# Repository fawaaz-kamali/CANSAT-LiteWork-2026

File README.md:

# CANSAT-LiteWork-2026
Repository containing major program files and schematics for Team 'Lite Work for the TMU CANSAT STEC Initiative 

Team Members: Fawaaz Kamali Siddiqui, Ben Reboks, Basim Allawala, Hamid Karimi, Mohammad Alwattar

## ESP32 Flight Computer

### Overview

The flight computer designed in the PDR phase of the competition is simply named the ESP32 Flight Computer. The circuit was designed 
entirely in KiCad and the microcontroller for the circuit is the ESP32-S3-WROOM-1. 

The parts list for this circuit is as follows:

| Model | Description |
|---|---|
| ESP32-S3-WROOM-1 | Microcontroller Unit |
| ICM-42670-L | Inertial Measurement Unit |
| ICP-20100 | Barometric Pressure Sensor |
| NEO-6M Breakout Board | GPS Module |
| 2 x SG90 | Servo Motors |
| 1S 18605 LiFePO4 | Battery |

#### KiCad Files
<div align="center">
  <div>

    <p><em>3D Render</em></p>
  </div>
  <br>

  <div>
    <br>
    <p><em>Schematic</em></p>
  </div>
  <br>
  
  <div>
    
    <br>
    <em>Footprint</em>
  </div>
</div>

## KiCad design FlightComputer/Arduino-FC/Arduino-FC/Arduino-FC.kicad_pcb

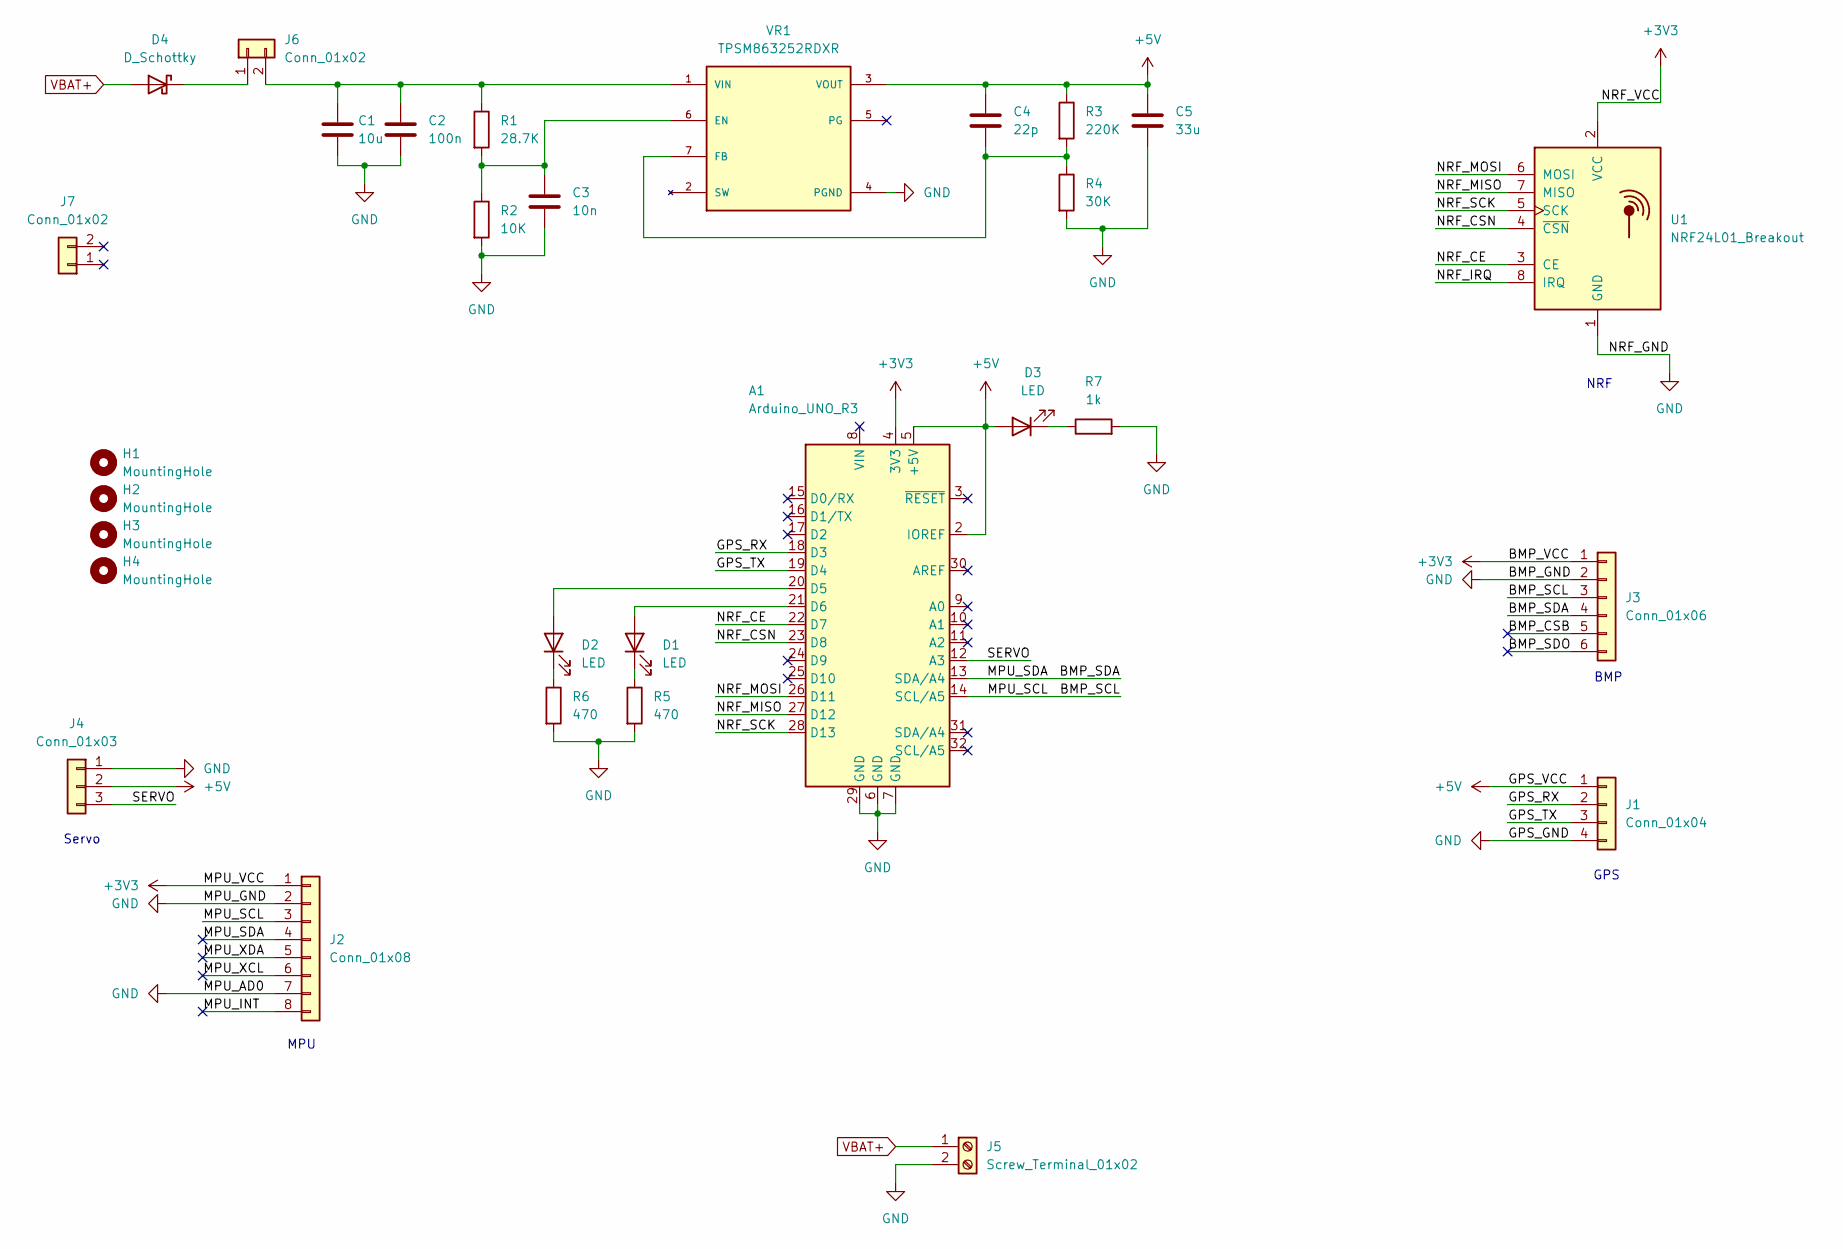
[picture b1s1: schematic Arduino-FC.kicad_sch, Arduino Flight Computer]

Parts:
A1: Arduino_UNO_R3
C1: 10u; C_0805_2012Metric_Pad1.18x1.45mm_HandSolder
C2: 100n; C_0805_2012Metric_Pad1.18x1.45mm_HandSolder
C3: 10n; C_0402_1005Metric_Pad0.74x0.62mm_HandSolder
C4: 22p; C_0402_1005Metric_Pad0.74x0.62mm_HandSolder
C5: 33u; C_1812_4532Metric_Pad1.57x3.40mm_HandSolder
D1, D2, D3: LED; LED_D5.0mm_Clear
D4: D_Schottky; DO-214AC
H1, H2, H3, H4: MountingHole; MountingHole_2.2mm_M2
J1: Conn_01x04; PinHeader_1x04_P2.54mm_Vertical
J2: Conn_01x08; PinHeader_1x08_P2.54mm_Vertical
J3: Conn_01x06; PinHeader_1x06_P2.54mm_Vertical
J4: Conn_01x03; PinHeader_1x03_P2.54mm_Vertical
J5: Screw_Terminal_01x02; TerminalBlock_MaiXu_MX126-5.0-02P_1x02_P5.00mm; LCSC C8465
J6, J7: Conn_01x02; PinHeader_1x02_P2.54mm_Vertical
R1: 28.7K; R_0402_1005Metric_Pad0.72x0.64mm_HandSolder
R2: 10K; R_0402_1005Metric_Pad0.72x0.64mm_HandSolder
R3: 220K; R_0603_1608Metric_Pad0.98x0.95mm_HandSolder
R4: 30K; R_0603_1608Metric_Pad0.98x0.95mm_HandSolder
R5, R6: 470; R_Axial_DIN0414_L11.9mm_D4.5mm_P15.24mm_Horizontal
R7: 1k; R_Axial_DIN0414_L11.9mm_D4.5mm_P15.24mm_Horizontal
U1: NRF24L01_Breakout; nRF24L01-Adapter
VR1: TPSM863252RDXR; VREG_TPSM863252RDXR; PARTREV B

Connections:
+3V3: A1.4 (3V3), J2.1, J3.1, U1.2 (VCC)
+5V: A1.2 (IOREF), A1.5 (+5V), C4.1, C5.1, D3.2 (A), J1.1, J4.2, R3.1, VR1.3 (VOUT)
/BMP_CSB: J3.5
/BMP_SCL: A1.14 (SCL/A5), J2.3, J3.3
/BMP_SDA: A1.13 (SDA/A4), J2.4, J3.4
/BMP_SDO: J3.6
/GPS_RX: A1.18 (D3), J1.2
/GPS_TX: A1.19 (D4), J1.3
/MPU_INT: J2.8
/MPU_XCL: J2.6
/MPU_XDA: J2.5
/NRF_CE: A1.22 (D7), U1.3 (CE)
/NRF_CSN: A1.23 (D8), U1.4 (~CSN)
/NRF_IRQ: U1.8 (IRQ)
/NRF_MISO: A1.27 (D12), U1.7 (MISO)
/NRF_MOSI: A1.26 (D11), U1.6 (MOSI)
/NRF_SCK: A1.28 (D13), U1.5 (SCK)
/SERVO: A1.12 (A3), J4.3
GND: A1.6 (GND), A1.7 (GND), A1.29 (GND), C1.2, C2.2, C3.2, C5.2, J1.4, J2.2, J2.7, J3.2, J4.1, J5.2, R2.2, R4.2, R5.2, R6.2, R7.2, U1.1 (GND), VR1.4 (PGND)
unnamed: A1.20 (D5), D2.2 (A)
unnamed: A1.21 (D6), D1.2 (A)
unnamed: D1.1 (K), R5.1
unnamed: D2.1 (K), R6.1
unnamed: D3.1 (K), R7.1
unnamed: D4.1 (K), J6.1
unnamed: C1.1, C2.1, J6.2, R1.1, VR1.1 (VIN)
unnamed: C3.1, R1.2, R2.1, VR1.6 (EN)
unnamed: C4.2, R3.2, R4.1, VR1.7 (FB)
VBAT+: D4.2 (A), J5.1

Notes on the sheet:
GPS
NRF
Servo
BMP
MPU

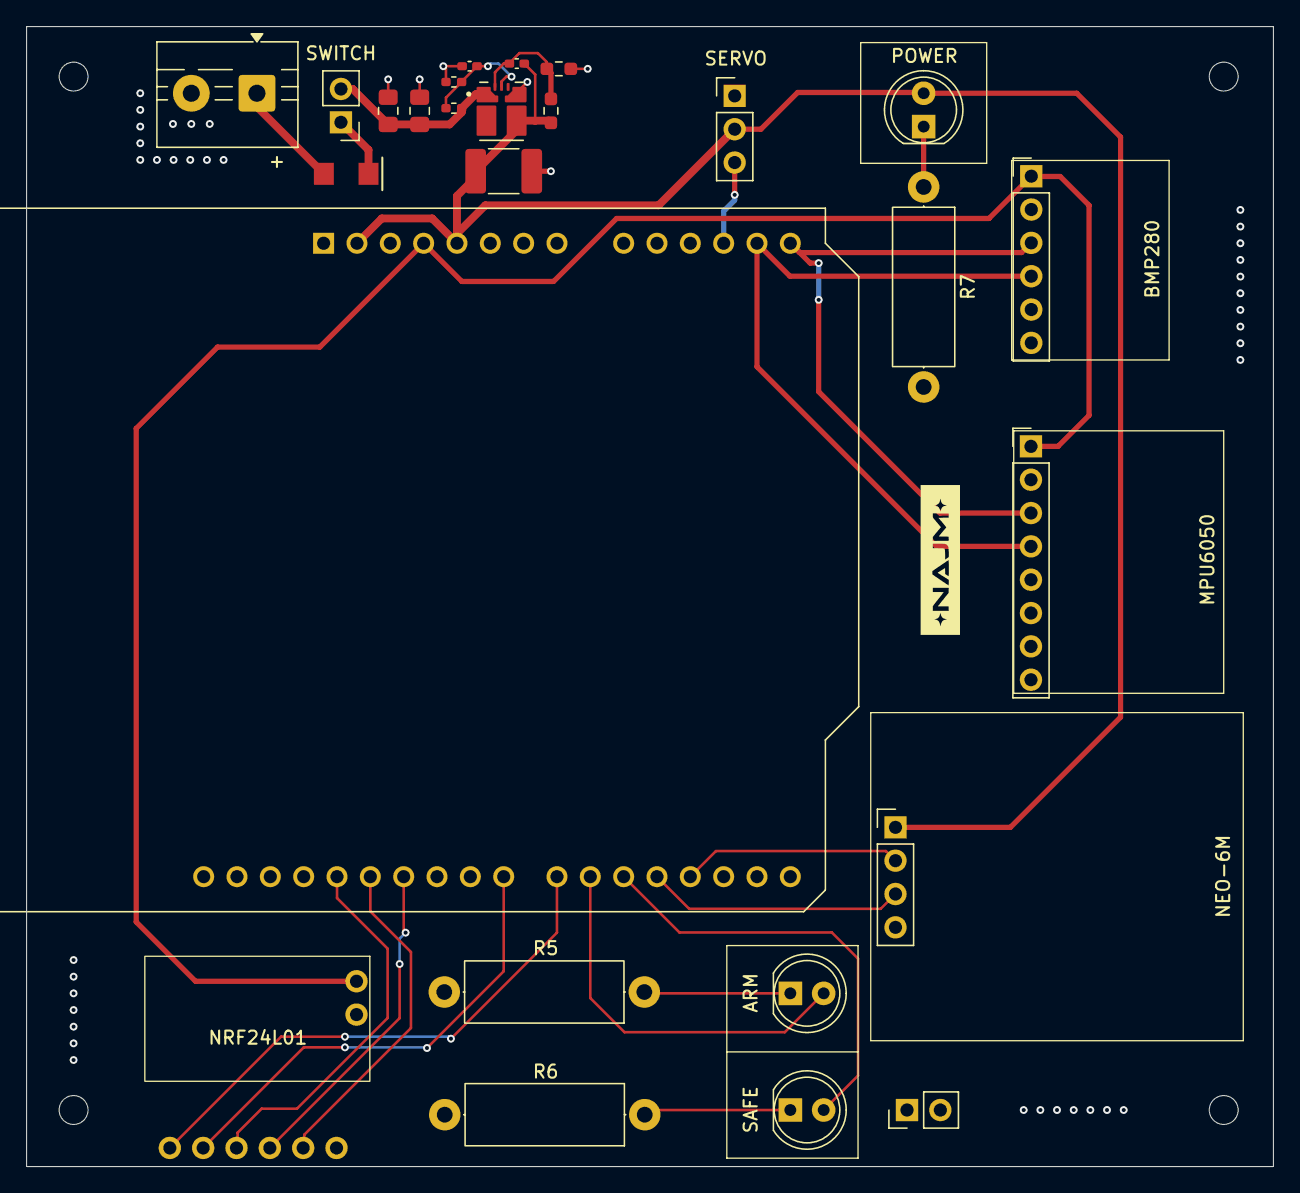
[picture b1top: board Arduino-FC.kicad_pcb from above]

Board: 2 copper layers, 95.0 x 86.9 mm, 30 parts (0 on the bottom side), 23 nets.

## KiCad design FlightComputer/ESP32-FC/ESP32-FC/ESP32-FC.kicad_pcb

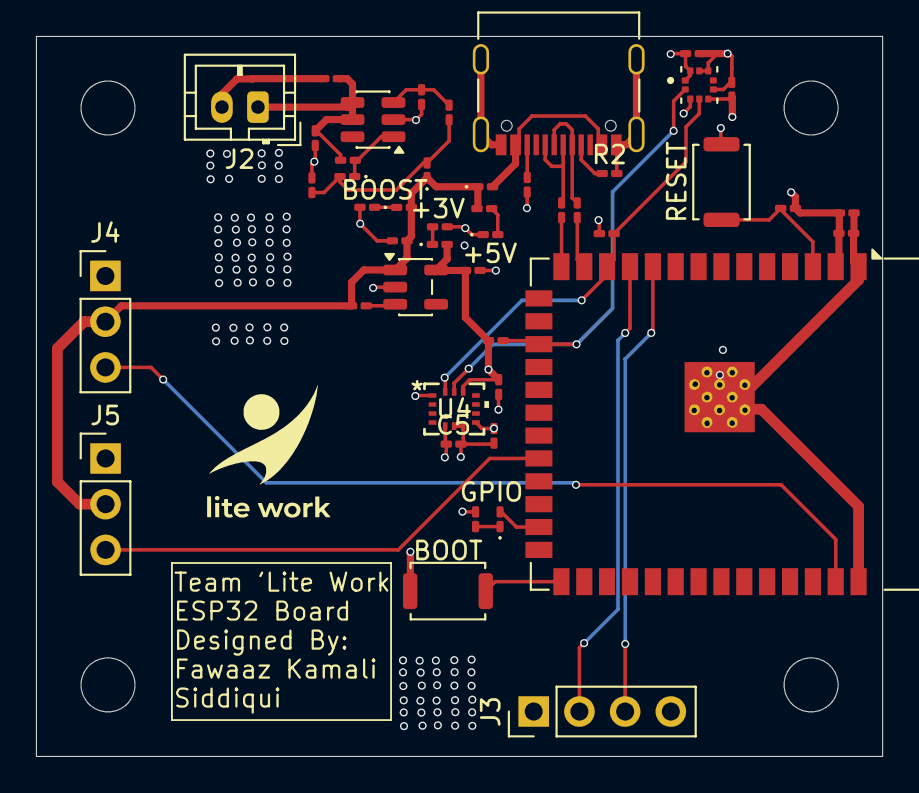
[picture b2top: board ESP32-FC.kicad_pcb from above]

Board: 4 copper layers, 47.0 x 40.0 mm, 50 parts (0 on the bottom side), 26 nets.

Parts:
+3V, +5V: LED; LED_0201_0603Metric_Pad0.64x0.40mm_HandSolder
BOOST: LED; LED_0201_0603Metric_Pad0.64x0.40mm_HandSolder
BOOT: BOOT; SW_Push_SPST_NO_Alps_SKRK
C1: 22uF; C_0201_0603Metric_Pad0.64x0.40mm_HandSolder
C2, C3, C6, C7: 0.1uF; C_0201_0603Metric_Pad0.64x0.40mm_HandSolder
C4: 2.2uF; C_0201_0603Metric_Pad0.64x0.40mm_HandSolder
C5: 10nF; C_0201_0603Metric_Pad0.64x0.40mm_HandSolder
C8, C9, C10, C11: C; C_0201_0603Metric_Pad0.64x0.40mm_HandSolder
D1, D2, D3: D_Schottky; D_0201_0603Metric_Pad0.64x0.40mm_HandSolder
GPIO: LED; LED_0201_0603Metric_Pad0.64x0.40mm_HandSolder
H1, H2, H3, H4: MountingHole; MountingHole_3mm
J1: USB_C_Receptacle_USB2.0_16P; USB_C_Receptacle_Palconn_UTC16-G
J2: Conn_01x02_Pin; JST_PH_B2B-PH-K_1x02_P2.00mm_Vertical
J3: Conn_01x04_Pin; PinHeader_1x04_P2.54mm_Vertical
J4, J5: Conn_01x03_Pin; PinHeader_1x03_P2.54mm_Vertical
L1: L; L_0201_0603Metric_Pad0.64x0.40mm_HandSolder
R1, R8, R9, R10, R11, R12, R13, R14, R15: R; R_0201_0603Metric_Pad0.64x0.40mm_HandSolder
R2, R3: 5K1; R_0201_0603Metric_Pad0.64x0.40mm_HandSolder
R4, R5: 27; R_0201_0603Metric_Pad0.64x0.40mm_HandSolder
R6, R7: 4K7; R_0201_0603Metric_Pad0.64x0.40mm_HandSolder
RESET: RESET; SW_Push_SPST_NO_Alps_SKRK
U1: ESP32-S3-WROOM-1
U2: AP2112K-3.3; SOT-23-5
U3: ICP-20100; PQFN50P200X200X85-10N
U4: ICM-42670-P; LGA14_2.5X3X0.76_IVS-L
U5: MT3608; SOT-23-6

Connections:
+3V3: +3V.2 (A), C1.1, C2.1, C3.1, C4.1, C5.1, C6.2, C7.1, C11.1, J3.4, R6.1, R7.1, R15.1, U1.2 (3V3), U2.5 (VOUT), U3.1 (CSB), U3.5 (VDD), U3.10 (VDDIO), U4.5 (VDDIO), U4.8 (VDD), U4.12 (AP_CS)
+5V: BOOST.2 (A), C10.1, D2.1 (K), D3.1 (K), J4.2, J5.2, R11.1, R12.1, U2.1 (VIN)
/EN: R15.2, RESET.2, U1.3 (EN)
/ESP_RX: J3.2, U1.11 (IO18)
/ESP_TX: J3.3, U1.10 (IO17)
/SCL: R7.2, U1.17 (IO9), U3.2 (SCL), U4.13 (AP_SCL/AP_SCLK)
/SDA: R6.2, U1.12 (IO8), U3.4 (SDA/SDIO/SDI), U4.14 (AP_SDA/AP_SDIO/AP_SDI)
/SERVO1: J4.3, U1.39 (IO1)
/SERVO2: J5.3, U1.22 (IO14)
GND: +5V.1 (K), BOOT.1, C1.2, C2.2, C3.2, C4.2, C5.2, C6.1, C7.2, C8.2, C9.2, C10.2, C11.2, J1.A1 (GND), J1.A12 (GND), J1.B1 (GND), J1.B12 (GND), J1.S1 (SHIELD), J2.2, J3.1, J4.1, J5.1, R1.2, R2.2, R3.2, R9.2, R10.2, R13.1, R14.1, RESET.1, U1.1 (GND), U1.40 (GND), U1.41 (GND), U2.2 (GND), U3.3 (VSS), U3.6 (SDO/AD0), U3.8 (RESV), U3.9 (RESV), U4.1 (AP_SDO/AP_AD0), U4.6 (GND), U4.7 (FSYNC), U5.2 (GND)
unnamed: C9.1, D1.2 (A), D2.2 (A), R8.1
unnamed: D1.1 (K), L1.2, U5.1 (SW)
unnamed: D3.2 (A), J1.A4 (VBUS), J1.A9 (VBUS), J1.B4 (VBUS), J1.B9 (VBUS)
unnamed: +5V.2 (A), R12.2
unnamed: BOOST.1 (K), R13.2
unnamed: +3V.1 (K), R14.2
unnamed: GPIO.2 (A), U1.25 (IO48)
unnamed: GPIO.1 (K), R1.1
unnamed: J1.A5 (CC1), R2.1
unnamed: J1.B5 (CC2), R3.1
unnamed: BOOT.2, U1.27 (IO0)
unnamed: R11.2, U2.3 (EN)
unnamed: R8.2, R9.1, U5.3 (FB)
USB_D+: J1.A6 (D+), J1.B6 (D+), R5.1, R5.2, U1.14 (USB_D+)
USB_D-: J1.A7 (D-), J1.B7 (D-), R4.1, R4.2, U1.13 (USB_D-)
VBAT: C8.1, J2.1, L1.1, R10.1, U5.4 (EN), U5.5 (IN)

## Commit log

2026-03-08 Project Initialization
2026-03-08 Added USB Connection
2026-03-08 Added MPU
2026-03-09 Addd ICM
    - Removed MPU 6050
    - Added ICM-42670-P
2026-03-09 Added ICP
    - Added pressure sensor module
2026-03-09 add initial files for dashboard
2026-03-19 Layout Creation
2026-03-22 Updated power architecture
2026-03-22 Servo + LEDs
2026-03-22 Boot Config
2026-03-22 Part placement
2026-03-23 Layout Major
2026-03-23 Export STEP file
2026-03-23 Update schematic
2026-03-23 Schematic Plot
2026-03-23 Layout Plots
2026-03-23 3D Model Exports
2026-03-23 3D model images
2026-03-23 Enhance README with PCB 3D model image
    TODO:
    > Add svg image of schematic and layout
2026-03-25 Added Images
2026-03-25 Update README
    Added team members and detailed overview of the ESP32 Flight Computer, including parts list and KiCad files.
2026-04-30 Added second FC
2026-05-20 Added Main.ino
    Updated schematic connections
2026-05-21 Buck Converter
    Footprint assignments
2026-05-24 Layout created
2026-05-25 Custom NRF Adapter footprint
2026-05-25 Indicator LEDs + Screw terminal
2026-05-25 Added switch
2026-05-26 Buck Converter Updates
    - updated footprint + values
2026-05-26 Diode + Power Jumper
2026-05-26 Mounting Holes Added
2026-05-26 Design Constraints
2026-05-26 Major Layout + Logo
2026-05-26 Background Slikscreen
2026-05-26 updated resistor val
2026-05-26 Revert second logo
2026-05-26 Revert "Major Layout + Logo"
    This reverts commit 6804596b28cb7cea65c62195238a1a9f434acbb5.
2026-05-26 Bottom Routing Complete
2026-05-26 MPU + BMP Routing
2026-05-26 Buck Layout
    Update buck footprint
2026-05-26 Complete Layout 1
2026-05-27 Warnings Resolution
2026-05-27 DRC Resolutions
2026-05-27 Back Silkscreen Addition
2026-05-27 Created production files
2026-05-27 Created Logo Footprint
2026-05-27 Added Najm Logo
    - Remade production files
